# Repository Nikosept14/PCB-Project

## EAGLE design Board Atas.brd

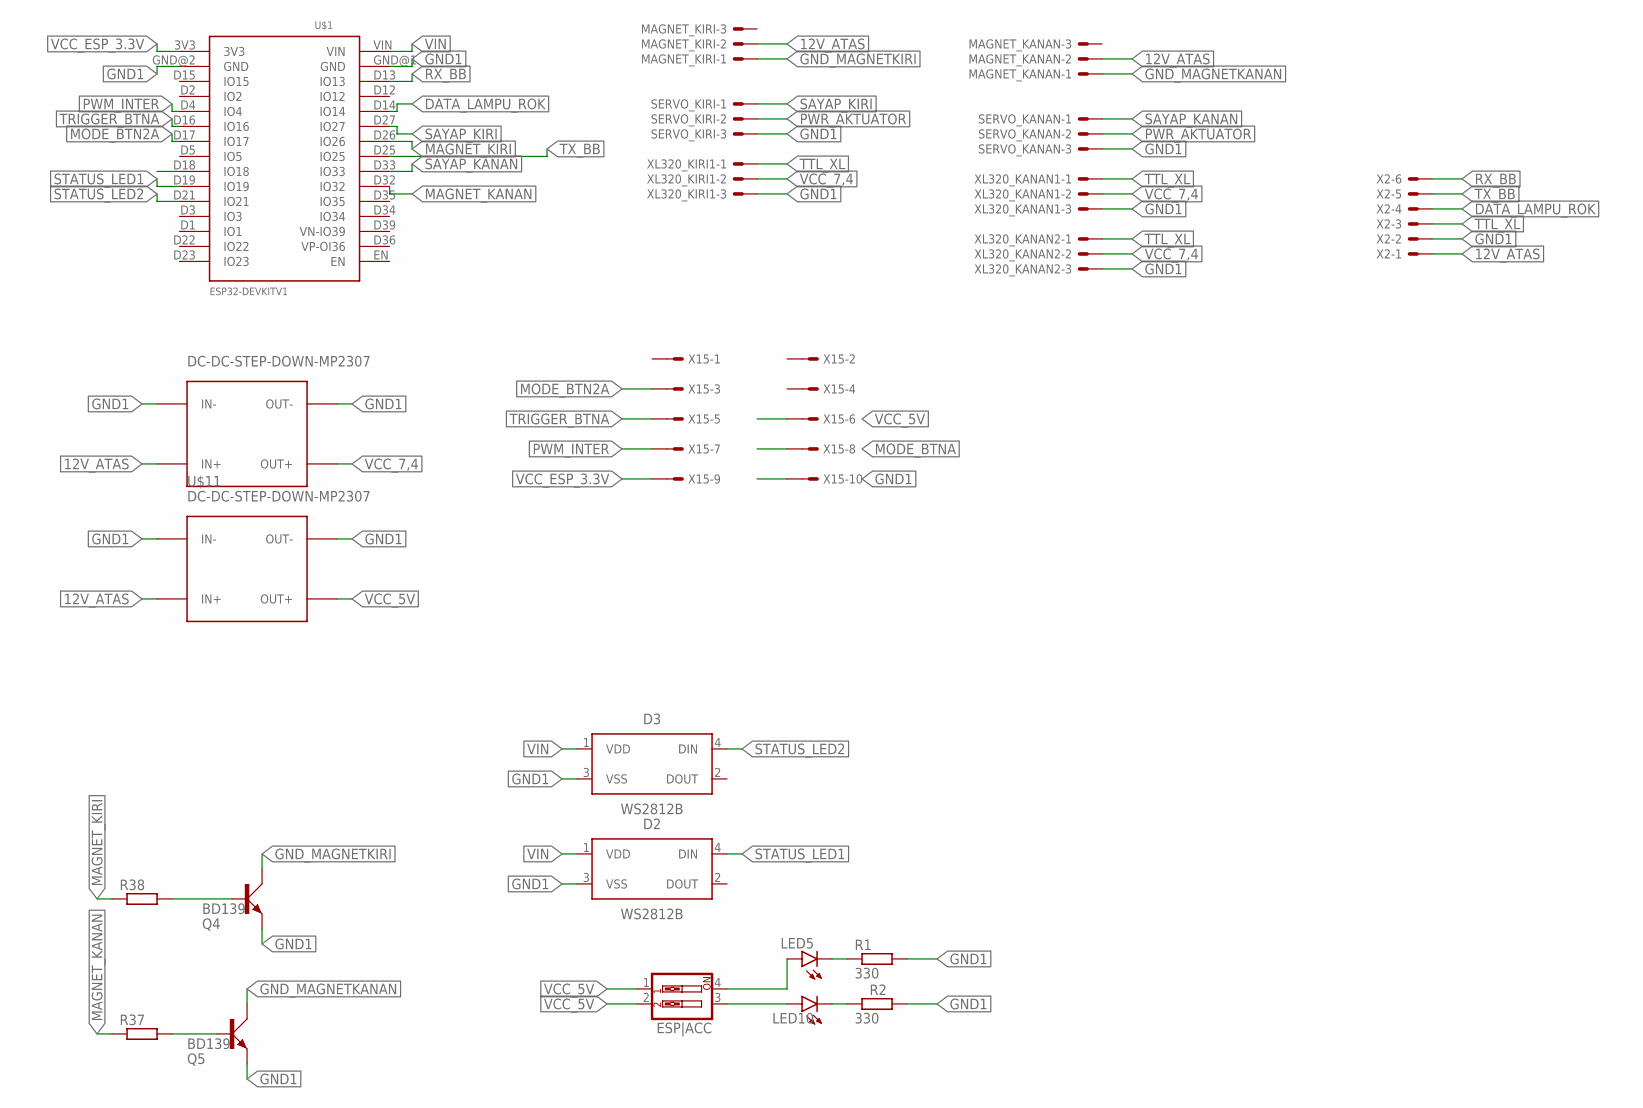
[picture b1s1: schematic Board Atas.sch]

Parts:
D2, D3: WS2812B
ESP|ACC: SW_DIP-2; EDG-02
LED5, LED10: LEDCHIPLED_1206; CHIPLED_1206
MAGNET_KANAN: 22-23-2031
MAGNET_KIRI: 22-23-2031
Q4, Q5: BD139; TO126AV
R1, R2: 330; M1206
R37, R38: R-EU_M0805; M0805
SERVO_KANAN: 22-23-2031
SERVO_KIRI: 22-23-2031
U$1: ESP32DEVKITV1; ESP32-DEVKITV1
U$8, U$11: DC-DC-STEP-DOWN-MP2307
X2: 22-23-2061
X15: 057-010-1
XL320_KANAN1, XL320_KANAN2, XL320_KIRI1: 22-23-2031

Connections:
12V_ATAS: MAGNET_KANAN.2, MAGNET_KIRI.2, U$8.IN+, U$11.IN+, X2.1
DATA_LAMPU_ROK: U$1.D14 (IO14), X2.4
GND1: D2.3 (VSS), D3.3 (VSS), Q4.E, Q5.E, R1.2, R2.2, SERVO_KANAN.3, SERVO_KIRI.3, U$1.GND@1 (GND), U$1.GND@2 (GND), U$8.IN-, U$8.OUT-, U$11.IN-, U$11.OUT-, X2.2, X15.10, XL320_KANAN1.3, XL320_KANAN2.3, XL320_KIRI1.3
GND_MAGNETKANAN: MAGNET_KANAN.1, Q5.C
GND_MAGNETKIRI: MAGNET_KIRI.1, Q4.C
MAGNET_KANAN: R37.1, U$1.D32 (IO32)
MAGNET_KIRI: R38.1, U$1.D26 (IO26)
MODE_BTN2A: U$1.D17 (IO17), X15.3
MODE_BTNA: U$1.D18 (IO18), X15.8
unnamed: LED5.C, R1.1
unnamed: LED10.C, R2.1
unnamed: Q4.B, R38.2
unnamed: Q5.B, R37.2
PWM_INTER: U$1.D4 (IO4), X15.7
PWR_AKTUATOR: ESP|ACC.3, LED10.A, SERVO_KANAN.2, SERVO_KIRI.2
RX_BB: U$1.D13 (IO13), X2.6
SAYAP_KANAN: SERVO_KANAN.1, U$1.D33 (IO33)
SAYAP_KIRI: SERVO_KIRI.1, U$1.D27 (IO27)
STATUS_LED1: D2.4 (DIN), U$1.D19 (IO19)
STATUS_LED2: D3.4 (DIN), U$1.D21 (IO21)
TRIGGER_BTNA: U$1.D16 (IO16), X15.5
TTL_XL: X2.3, XL320_KANAN1.1, XL320_KANAN2.1, XL320_KIRI1.1
TX_BB: U$1.D25 (IO25), X2.5
VCC_5V: ESP|ACC.1, ESP|ACC.2, U$11.OUT+, X15.6
VCC_7,4: U$8.OUT+, XL320_KANAN1.2, XL320_KANAN2.2, XL320_KIRI1.2
VCC_ESP_3.3V: U$1.3V3, X15.9
VIN: D2.1 (VDD), D3.1 (VDD), ESP|ACC.4, LED5.A, U$1.VIN

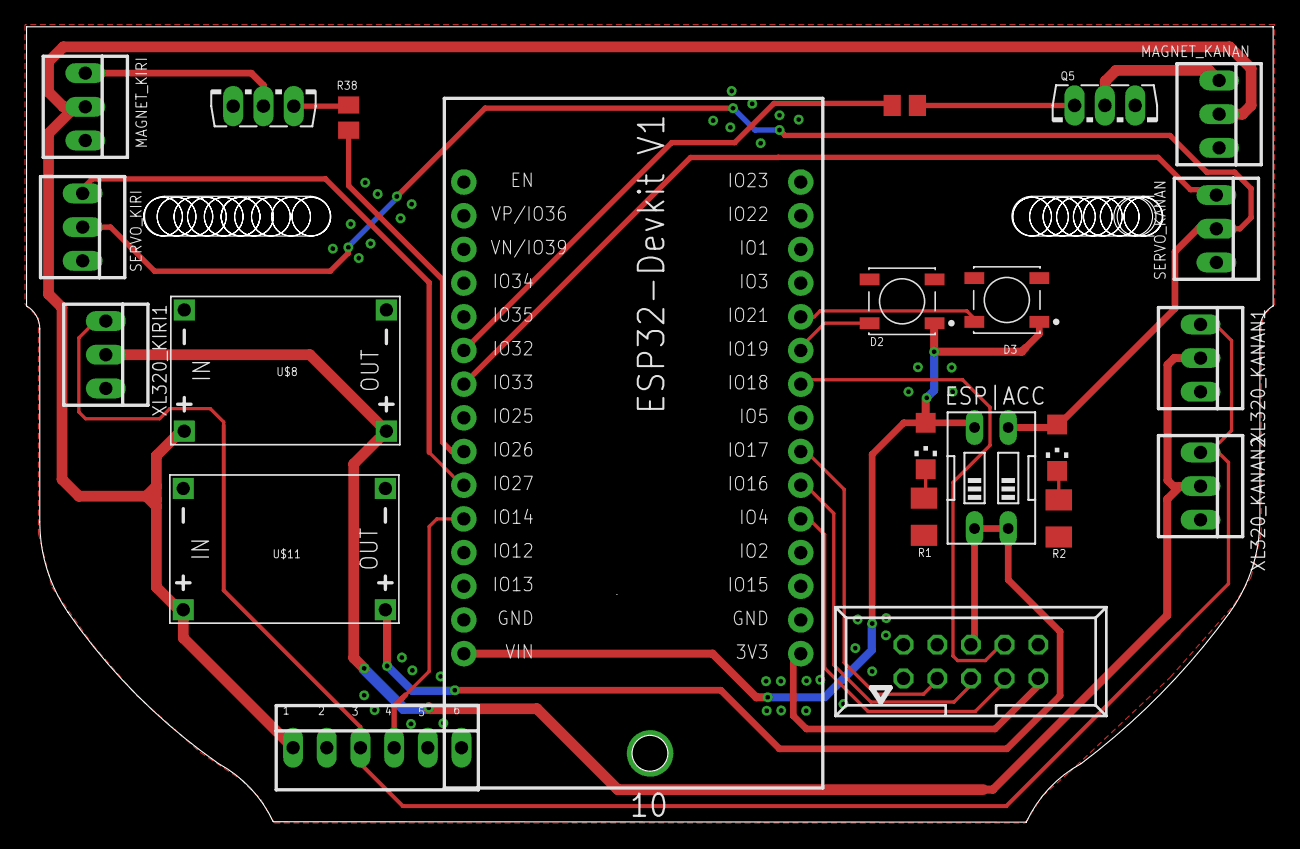
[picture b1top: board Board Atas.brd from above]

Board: 2 copper layers, 94.0 x 60.0 mm, 23 parts (0 on the bottom side), 27 nets.

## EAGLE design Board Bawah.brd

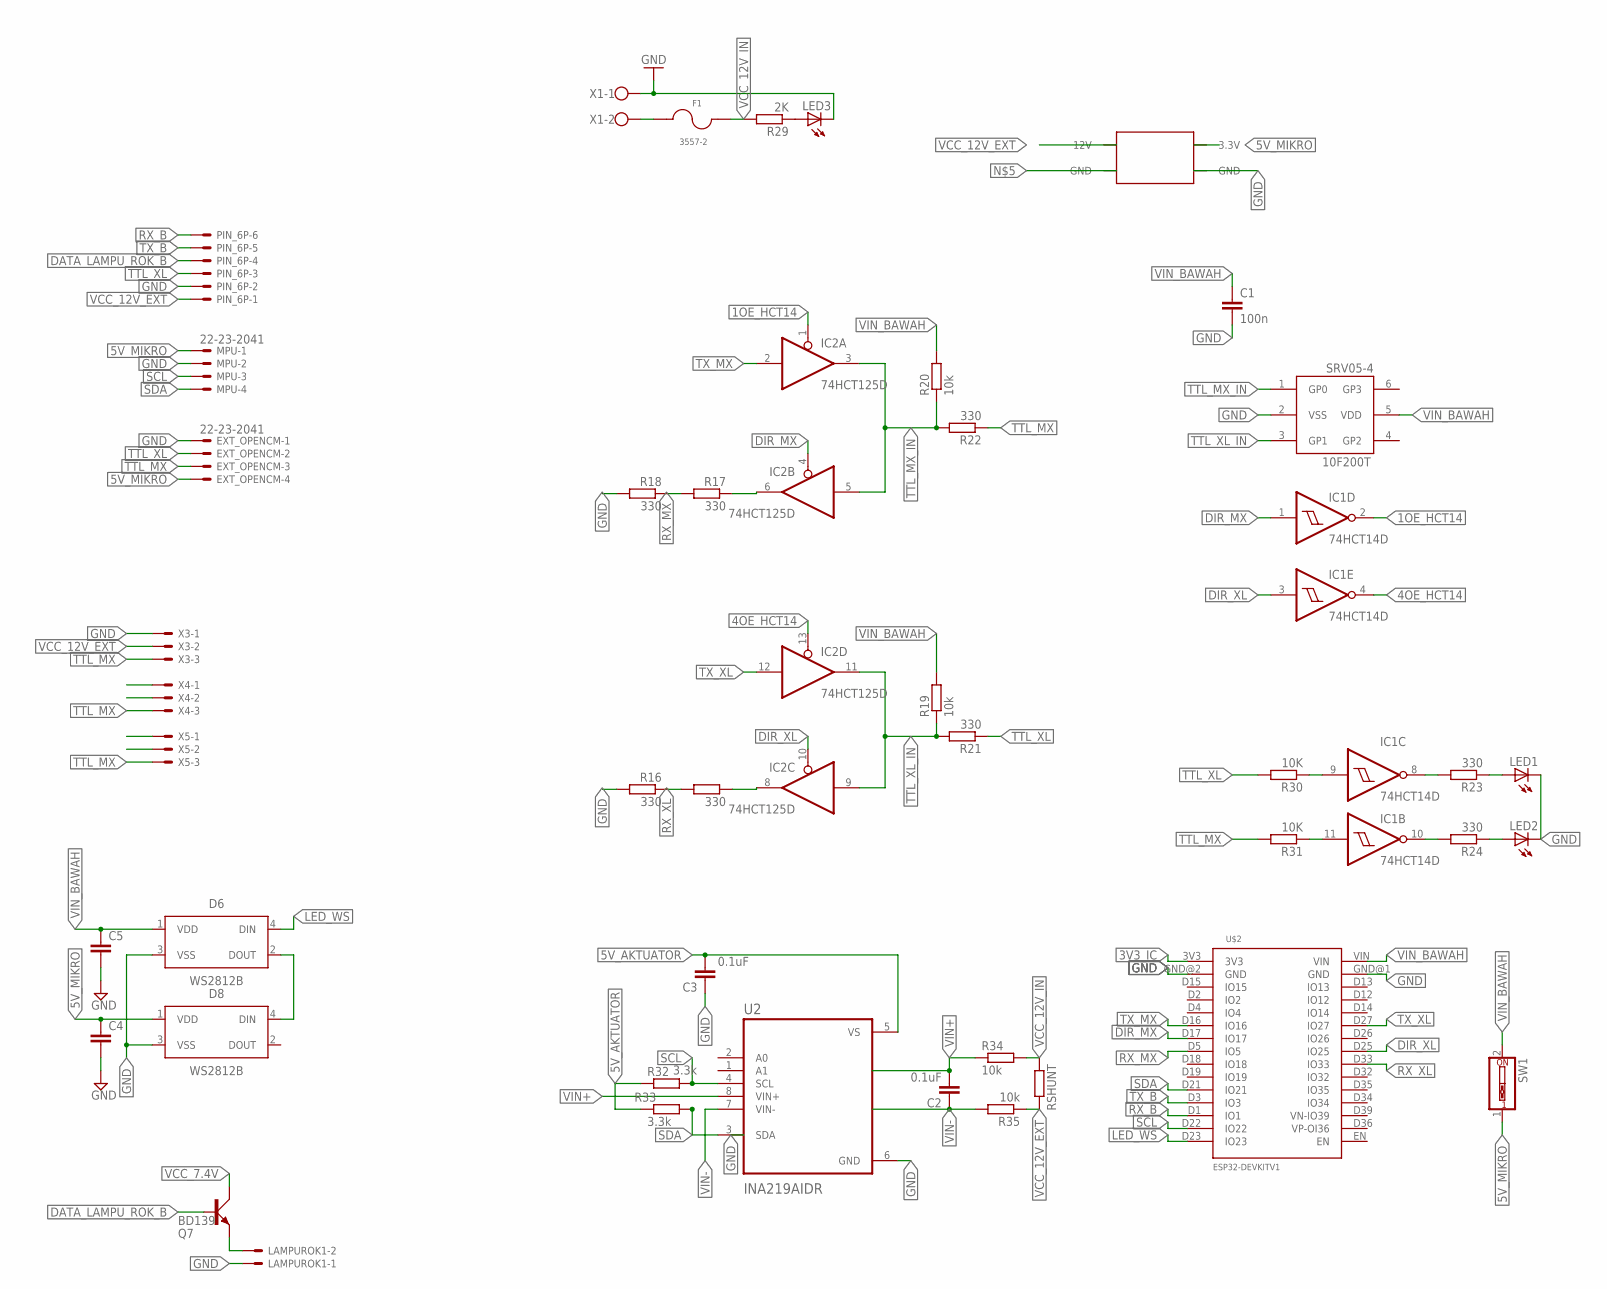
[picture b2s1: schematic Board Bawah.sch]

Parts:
C1: 100n; C0805
C2, C3: 0.1uF; C0805
C4, C5: C-EUC0805; C0805
D6, D8: WS2812B
EXT_OPENCM: 22-23-2041
F1: 3557-2; FUSE_3557-2
IC1: 74HCT14D; SO14
IC2: 74HCT125D; SO14
LAMPUROK1: 22-23-2021
LED1, LED2, LED3: LEDCHIPLED_1206; CHIPLED_1206
MPU: 22-23-2041
PIN_6P: 22-23-2061
Q7: BD139; TO126AV
R13, R16, R17, R18, R21, R22, R23, R24: 330; R0805
R19, R20, R34, R35: 10k; R0805
R29: 2K; R0805
R30, R31: 10K; R0805
R32, R33: 3.3k; R0805
RSHUNT: R-EU_R2512; R2512
SRV05-4: 10F200T; SOT23-6
SW1: SW_DIP-1; EDG-01
U2: INA219AIDR; SOIC127P599X175-8N
U$2: ESP32DEVKITV1; ESP32-DEVKITV1
U$5: MP2307-MINI-360
X1: W237-102
X3, X4, X5: 22-23-2031

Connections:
1OE_HCT14: IC1.2 (O), IC2.1 (OE)
3V3_IC: U$2.3V3
4OE_HCT14: IC1.4 (O), IC2.13 (OE)
5V_AKTUATOR: C3.2, R32.1, R33.1, U2.5 (VS)
5V_MIKRO: C4.1, D8.1 (VDD), EXT_OPENCM.4, MPU.1, SW1.1, U$5.V+OUT (3.3V)
DATA_LAMPU_ROK_B: PIN_6P.4, Q7.B
DIR_MX: IC1.1 (I), IC2.4 (OE), U$2.D17 (IO17)
DIR_XL: IC1.3 (I), IC2.10 (OE), U$2.D25 (IO25)
GND: C1.2, C3.1, C4.2, C5.2, D6.3 (VSS), D8.3 (VSS), EXT_OPENCM.1, IC1.7 (GND), IC2.7 (GND), LAMPUROK1.1, LED1.C, LED2.C, LED3.C, MPU.2, PIN_6P.2, R16.2, R18.2, SRV05-4.2 (VSS), U2.6 (GND), U$2.GND@1 (GND), U$2.GND@2 (GND), U$5.GND_OUT (GND), X1.1, X3.1, X4.1, X5.1
LED_WS: D6.4 (DIN), U$2.D23 (IO23)
unnamed: LAMPUROK1.2, Q7.E
unnamed: IC1.8 (O), R23.2
unnamed: IC1.9 (I), R30.1
unnamed: LED1.A, R23.1
unnamed: F1.1_1 (1), F1.1_2 (1), X1.2
unnamed: IC1.10 (O), R24.2
unnamed: LED2.A, R24.1
unnamed: LED3.A, R29.1
unnamed: IC1.11 (I), R31.1
unnamed: IC2.6 (O), R17.1
unnamed: IC2.8 (O), R13.1
unnamed: D6.2 (DOUT), D8.4 (DIN)
RX_B: PIN_6P.6, U$2.D1 (IO1)
RX_MX: R17.2, R18.1, U$2.D5 (IO5)
RX_XL: R13.2, R16.1, U$2.D33 (IO33)
SCL: MPU.3, R32.2, U2.4 (SCL), U$2.D22 (IO22)
SDA: MPU.4, R33.2, U2.3 (SDA), U$2.D21 (IO21)
TTL_MX: EXT_OPENCM.3, R22.1, R31.2, X3.3, X4.3, X5.3
TTL_MX_IN: IC2.3 (O), IC2.5 (I), R20.1, R22.2, SRV05-4.1 (GP0)
TTL_XL: EXT_OPENCM.2, PIN_6P.3, R21.1, R30.2
TTL_XL_IN: IC2.9 (I), IC2.11 (O), R19.1, R21.2, SRV05-4.3 (GP1)
TX_B: PIN_6P.5, U$2.D3 (IO3)
TX_MX: IC2.2 (I), U$2.D16 (IO16)
TX_XL: IC2.12 (I), U$2.D27 (IO27)
VCC_7.4V: Q7.C
VCC_12V_EXT: PIN_6P.1, R35.1, RSHUNT.2, U$5.V+IN (12V), X3.2, X4.2, X5.2
VCC_12V_IN: F1.2_1 (2), F1.2_2 (2), R29.2, R34.2, RSHUNT.1
VIN+: C2.2, R34.1, U2.8 (VIN+)
VIN-: C2.1, R35.2, U2.7 (VIN-)
VIN_BAWAH: C1.1, C5.1, D6.1 (VDD), IC1.14 (VIN_BAWAH), IC2.14 (VIN_BAWAH), R19.2, R20.2, SRV05-4.5 (VDD), SW1.2, U$2.VIN

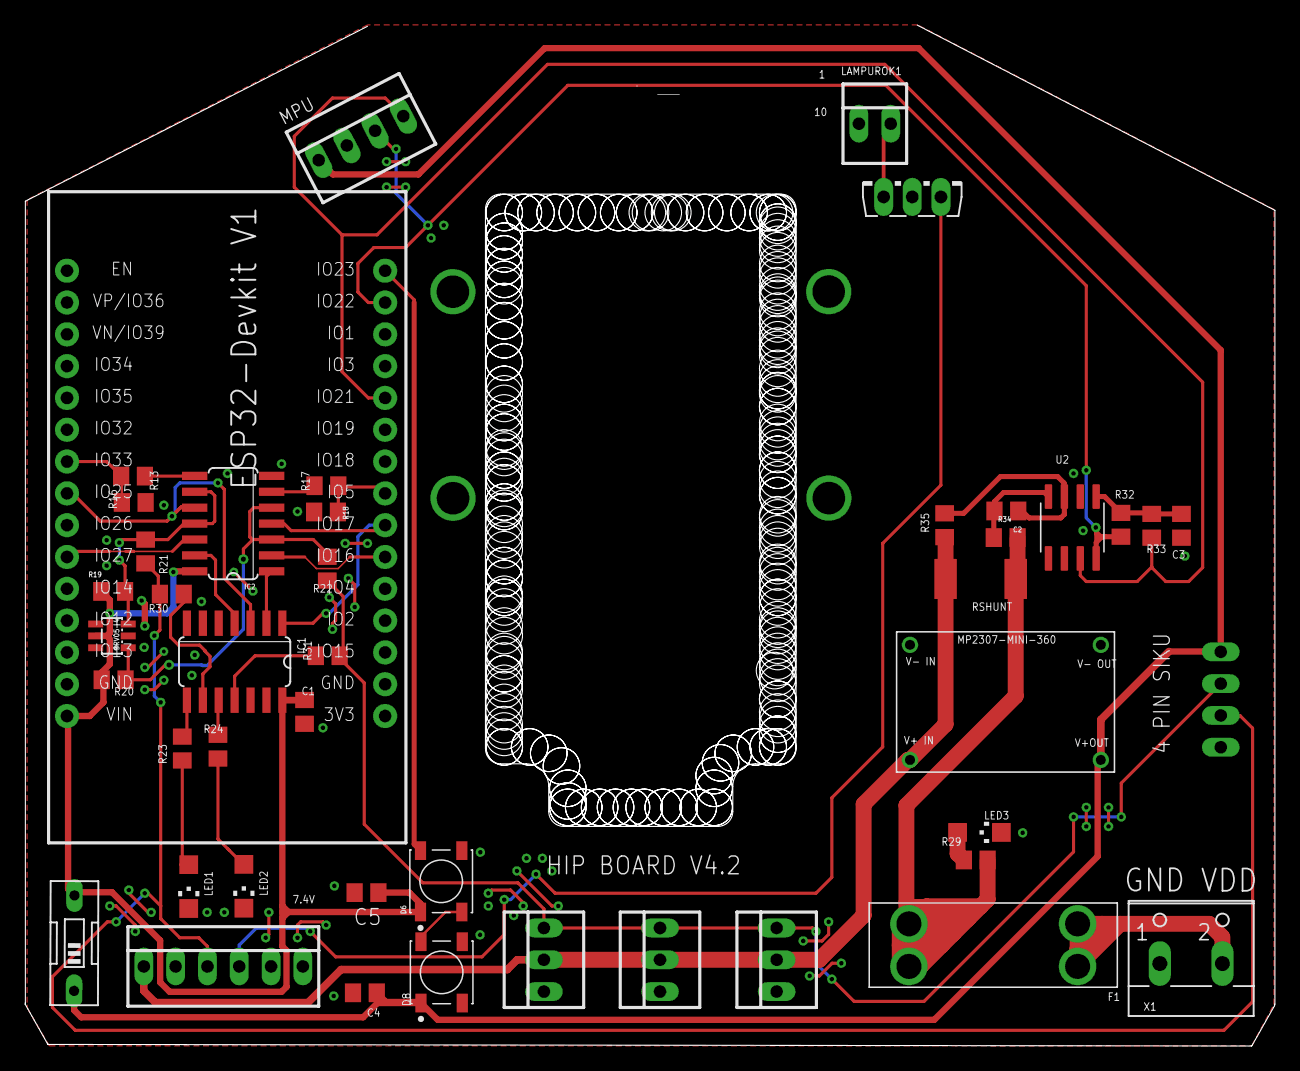
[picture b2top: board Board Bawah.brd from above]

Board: 2 copper layers, 99.8 x 81.5 mm, 45 parts (1 on the bottom side), 38 nets.

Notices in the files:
parts and their libraries:
diy-modules: Released under the Creative Commons Attribution 4.0 International License: http://creativecommons.org/licenses/by/4.0
